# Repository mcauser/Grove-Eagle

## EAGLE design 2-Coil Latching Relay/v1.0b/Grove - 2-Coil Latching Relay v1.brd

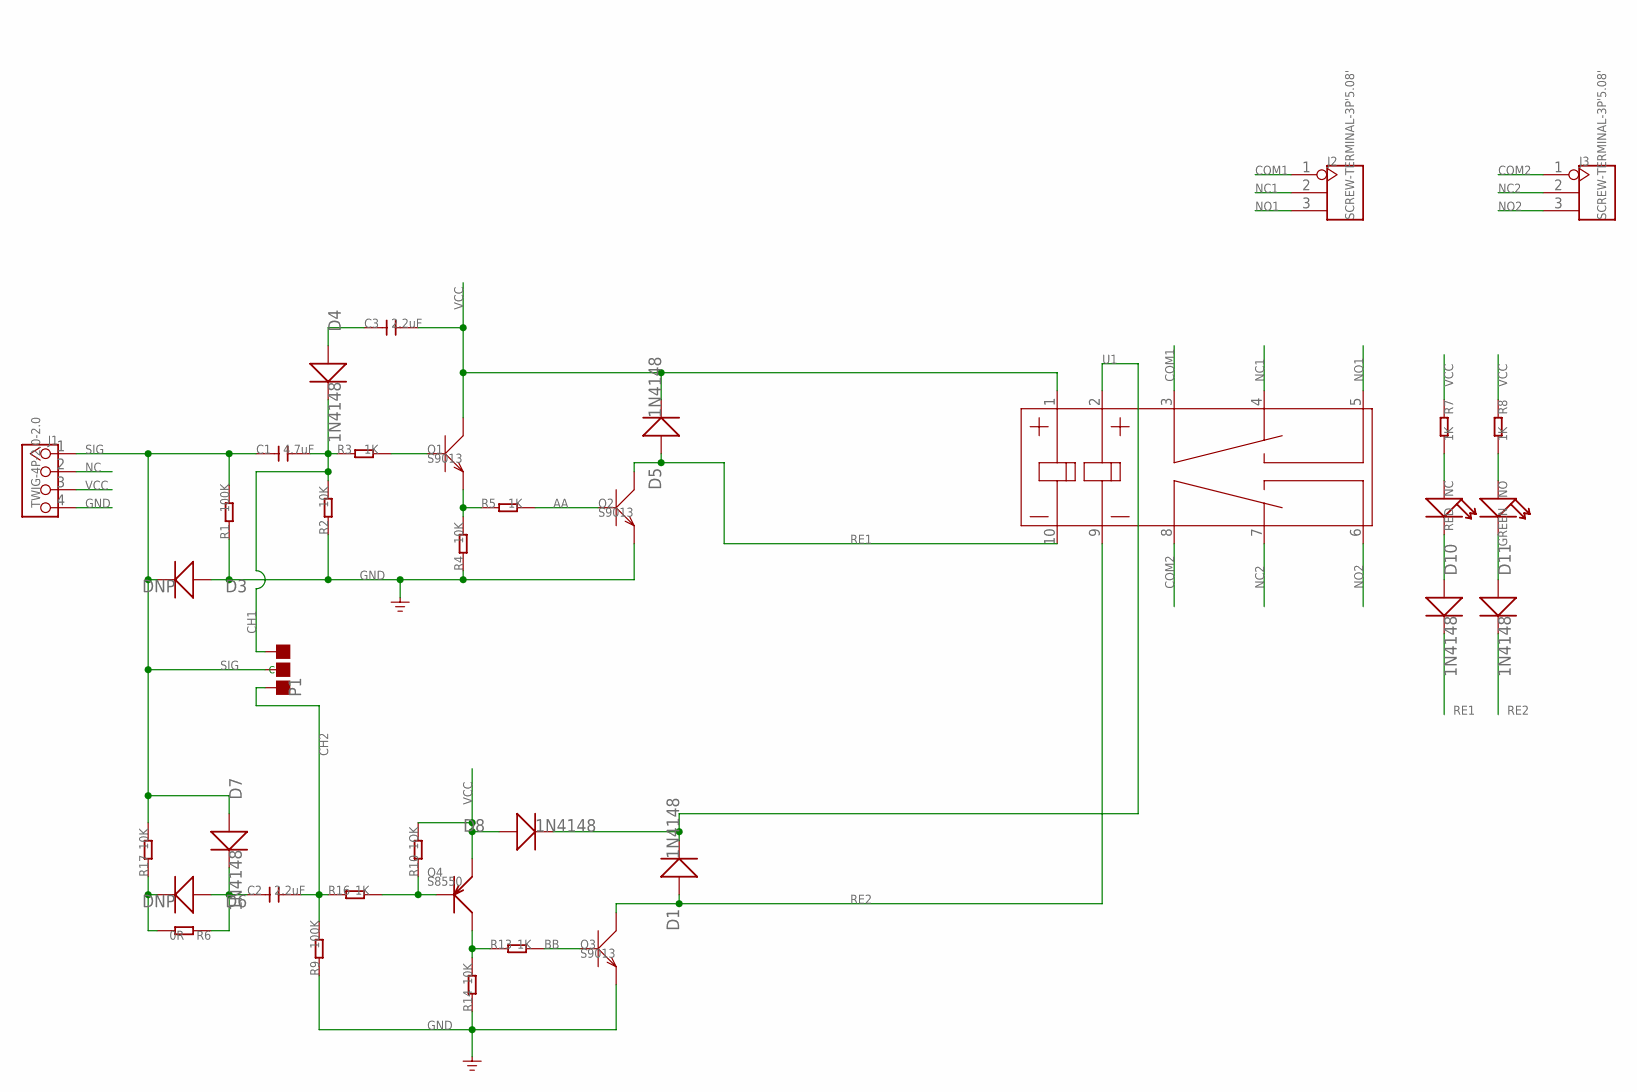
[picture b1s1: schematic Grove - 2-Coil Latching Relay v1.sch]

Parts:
C1: 4.7uF; C0805
C2, C3: 2.2uF; C0805
D1, D4, D5, D7, D8, D10, D11: 1N4148; DO-35-SMD
D3, D6: DNP; DO-35-SMD
J1: TWIG-4P-2.0-2.0; 4P-2.0
J2, J3: SCREW-TERMINAL-3P'5.08'; 3P-5.08
NC: RED; LED-0603
NO: GREEN; LED-0603
P1: PAD-JUMPER-3P-40*40; 3P-SMD-4.1X1.5
Q1, Q2, Q3: S9013; SOT23
Q4: S8550; SOT23
R1, R9: 100K; R0603
R2, R4, R14, R17: 10K; R0603
R3, R5, R7, R8, R13, R16: 1K; R0603
R6: 0R; R0603
R10: 1OK; R0603
U1: RELAY-HFD2/005-S-L2'HFD2/005-S-L2'; 10P-20.2X10.2X10.6

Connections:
AA: Q2.1 (B), R5.2
BB: Q3.1 (B), R13.2
CH1: C1.2, D4.C (-), P1.00 (L), R2.2, R3.1
CH2: C2.2, P1.11 (R), R9.2, R16.1
COM1: J2.1, U1.3 (4)
COM2: J3.1, U1.8 (13)
GND: D3.A (+), J1.4, Q2.2 (E), Q3.2 (E), R1.1, R2.1, R4.1, R9.1, R14.1
unnamed: NO.+, R8.2
unnamed: C3.1, D4.A (+)
unnamed: Q1.1 (B), R3.2
unnamed: Q1.2 (E), R4.2, R5.1
unnamed: D10.A (+), NC.-
unnamed: D11.A (+), NO.-
unnamed: NC.+, R7.2
unnamed: D6.C (-), R6.2, R17.1
unnamed: C2.1, D6.A (+), D7.C (-), R6.1
unnamed: Q4.1 (B), R10.1, R16.2
unnamed: D1.C (-), D8.C (-), U1.2
unnamed: Q4.3 (C), R13.1, R14.2
NC: J1.2
NC1: J2.2, U1.4 (6)
NC2: J3.2, U1.7 (11)
NO1: J2.3, U1.5 (8)
NO2: J3.3, U1.6 (9)
RE1: D5.A (+), D10.C (-), Q2.3 (C), U1.10 (16)
RE2: D1.A (+), D11.C (-), Q3.3 (C), U1.9 (15)
SIG: C1.1, D3.C (-), D7.A (+), J1.1, P1.MM (C), R1.2, R17.2
VCC: C3.2, D5.C (-), D8.A (+), J1.3, Q1.3 (C), Q4.2 (E), R7.1, R8.1, R10.2, U1.1

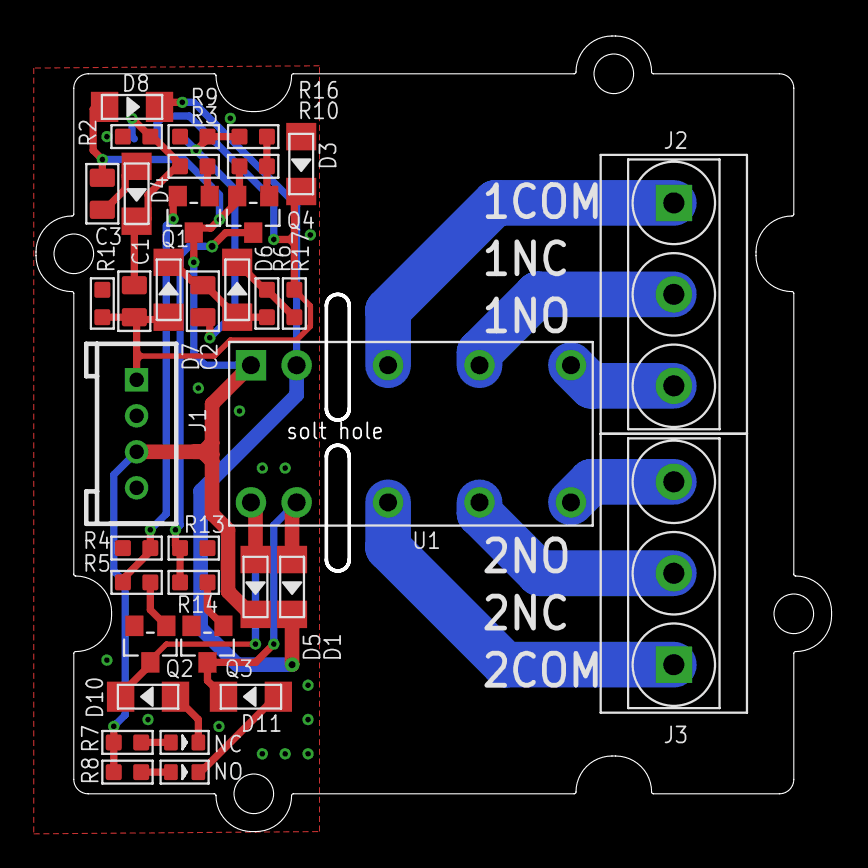
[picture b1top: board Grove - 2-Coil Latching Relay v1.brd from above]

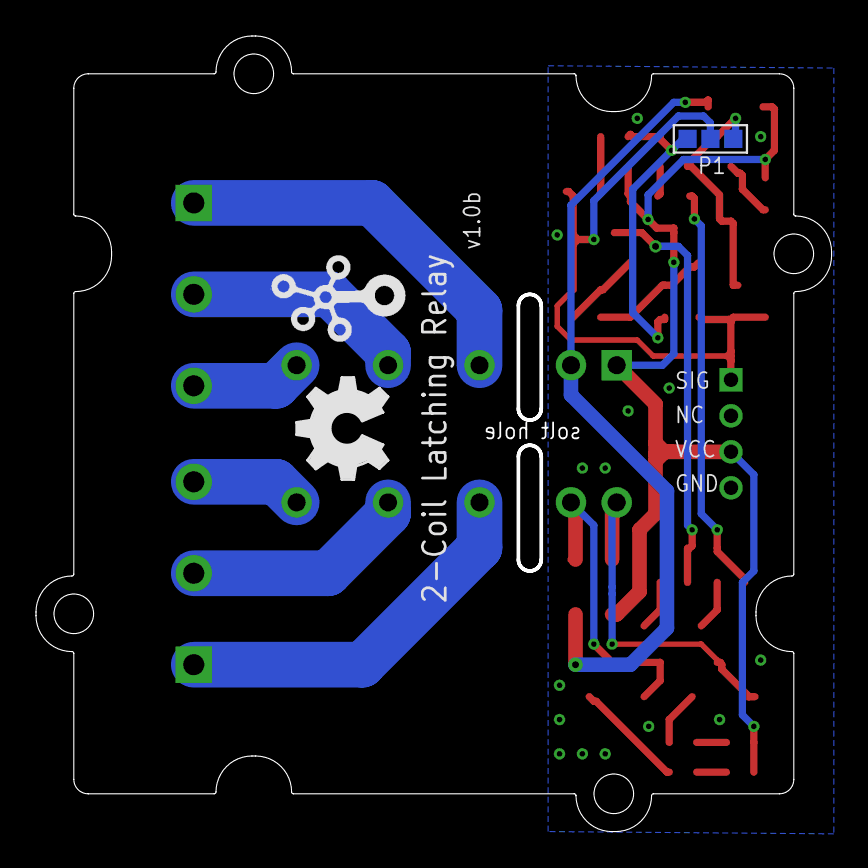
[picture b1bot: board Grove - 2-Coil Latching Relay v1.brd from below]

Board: 2 copper layers, 44.2 x 44.2 mm, 40 parts (3 on the bottom side), 27 nets.

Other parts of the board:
U$4: 2X2U-DIM-W/-DRILL
U$5: OSHW_FILLX200_NOTEXT
U$6: TWIGLOGO

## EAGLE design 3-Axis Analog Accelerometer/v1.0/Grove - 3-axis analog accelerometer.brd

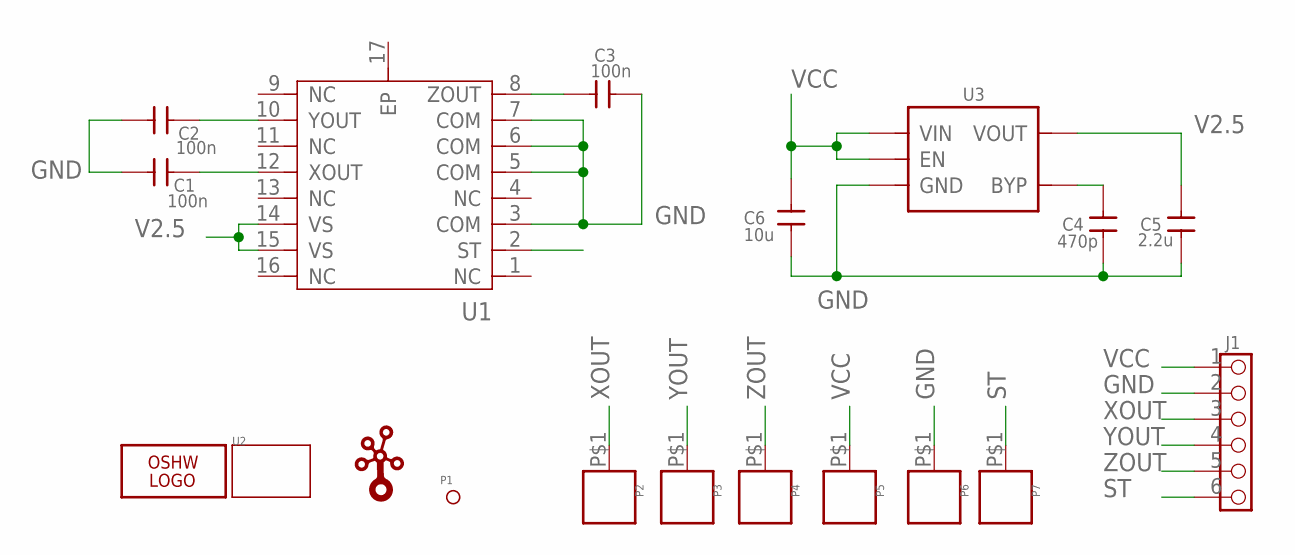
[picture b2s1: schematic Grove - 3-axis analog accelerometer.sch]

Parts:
C1, C2, C3: 100n; 0402
C4: 470p; 0603
C5: 2.2u; 0603
C6: 10u; 0603
J1: HEADER-6P-60/35MIL; 6P-2.54-60/35MIL
LOGO2: LOGO-OSHW-6MILX0200-NT; OSHW_6X200_NOTEXT
P1: PAD-MARK; ROUND-MARK-0.635
P2, P3, P4, P5, P6, P7: PAD'1X2MM'; 1P-1X2
U1: ADXL335; LFCSP16-4X4
U2: TWIG-1U; 1U-DIM-W/-DRILL
U3: MIC5205; SOT23-5
U$1: LOGO-TWIGTWIGLOGO_SMALL; TWIGLOGO_SMALL

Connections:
GND: C1.1, C2.2, C3.1, C4.1, C5.1, C6.1, J1.2, P6.P$1, U1.3 (COM), U1.5 (COM), U1.6 (COM), U1.7 (COM), U3.2 (GND)
unnamed: C4.2, U3.4 (BYP)
ST: J1.6, P7.P$1, U1.2 (ST)
V2.5: C5.2, U1.14 (VS), U1.15 (VS), U3.5 (VOUT)
VCC: C6.2, J1.1, P5.P$1, U3.1 (VIN), U3.3 (EN)
XOUT: C1.2, J1.3, P2.P$1, U1.12 (XOUT)
YOUT: C2.1, J1.4, P3.P$1, U1.10 (YOUT)
ZOUT: C3.2, J1.5, P4.P$1, U1.8 (ZOUT)

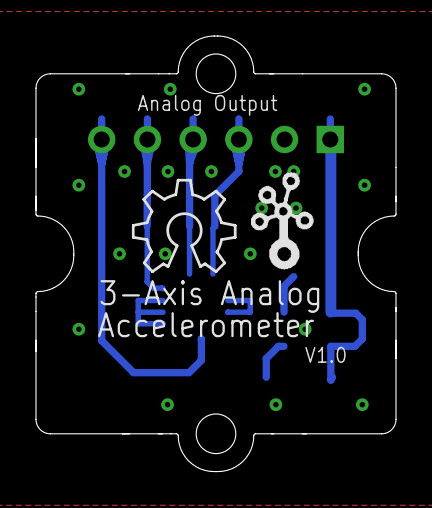
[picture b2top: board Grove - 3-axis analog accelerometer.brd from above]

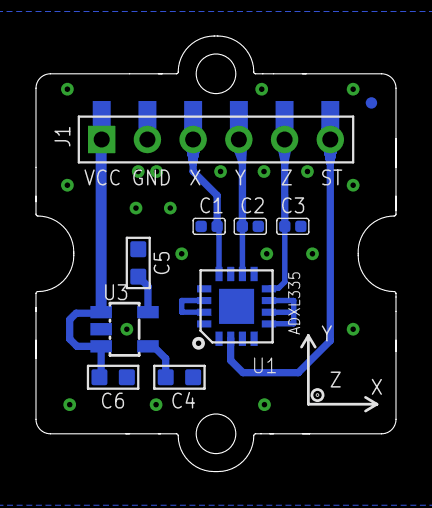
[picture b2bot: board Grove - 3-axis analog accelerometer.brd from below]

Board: 2 copper layers, 20.0 x 24.2 mm, 19 parts (17 on the bottom side), 8 nets.

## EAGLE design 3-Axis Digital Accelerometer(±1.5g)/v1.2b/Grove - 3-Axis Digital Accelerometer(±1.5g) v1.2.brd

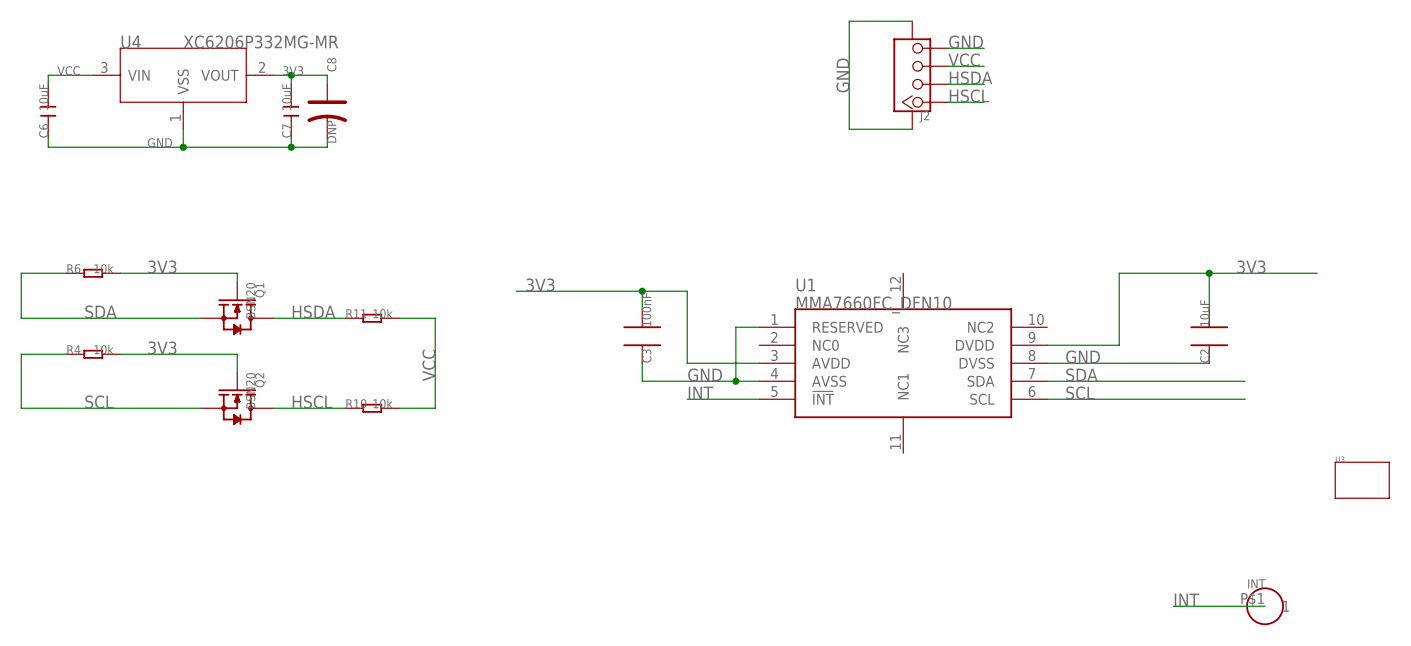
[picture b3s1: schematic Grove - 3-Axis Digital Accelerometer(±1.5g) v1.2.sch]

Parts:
C2: 10uF; 0805_S
C3: 100nF; 0603_S
C6, C7: 10uF; C0805
C8: DNP; AVX-A
INT: HEADER-1P-35; 1P-65/35MIL
J2: TWIG-4P-2.0-SMD-FEMALE-REINFORCE'DD'; 4P-SMD-2.0
Q1, Q2: BSN20; SOT23
R4, R6, R10, R11: 10k; R0603
U1: MMA7660FC_DFN10; DFN10
U3: TWIG-1U; 1U-DIM-W/-DRILL
U4: XC6206P332MG-MR; SOT23

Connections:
3V3: C2.2, C3.2, C7.2, C8.+, Q1.1 (G), Q2.1 (G), R4.2, R6.2, U1.3 (AVDD), U1.9 (DVDD), U4.2 (VOUT)
GND: C2.1, C3.1, C6.1, C7.1, C8.-, J2.4, J2.SS1, J2.SS2, U1.1 (RESERVED), U1.4 (AVSS), U1.8 (DVSS), U4.1 (VSS)
HSCL: J2.1, Q2.3 (D), R10.1
HSDA: J2.2, Q1.3 (D), R11.1
INT: INT.P$1, U1.5 (!INT)
SCL: Q2.2 (S), R4.1, U1.6 (SCL)
SDA: Q1.2 (S), R6.1, U1.7 (SDA)
VCC: C6.2, J2.3, R10.2, R11.2, U4.3 (VIN)

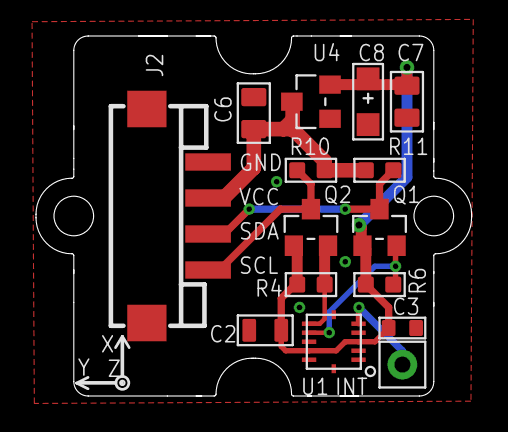
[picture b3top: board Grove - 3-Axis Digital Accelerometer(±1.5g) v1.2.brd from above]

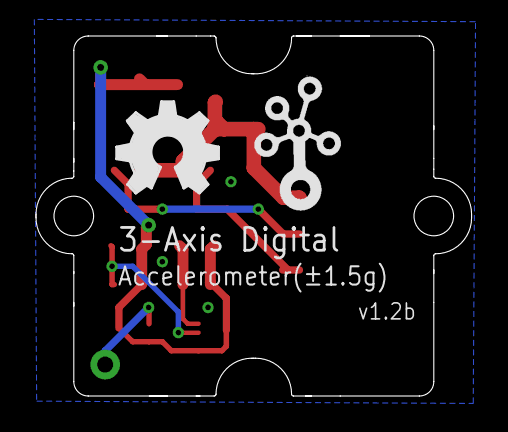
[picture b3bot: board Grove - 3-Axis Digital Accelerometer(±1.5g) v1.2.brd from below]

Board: 2 copper layers, 24.2 x 20.0 mm, 18 parts (2 on the bottom side), 8 nets.

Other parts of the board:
U$1: OSHW_FILLX200_NOTEXT
U$3: TWIGLOGO

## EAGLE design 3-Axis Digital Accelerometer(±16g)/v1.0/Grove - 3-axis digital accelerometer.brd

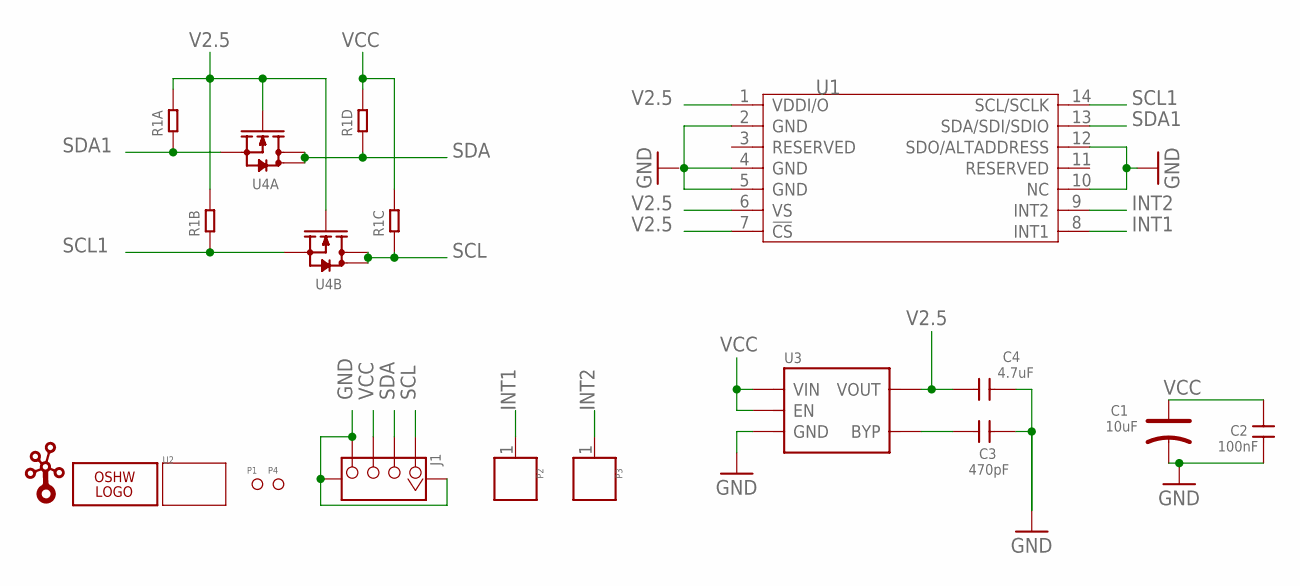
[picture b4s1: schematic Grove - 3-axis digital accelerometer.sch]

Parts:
C1: 10uF; AVX-A
C2: 100nF; 0603
C3: 470pF; 0603
C4: 4.7uF; 0603
J1: TWIG-4P-2.0-SMD-FEMALE-REINFORCE'DD'; 4P-SMD-2.0
LOGO1: LOGO-OSHW-6MILX0200-NT; OSHW_6X200_NOTEXT
P1, P4: PAD-MARK; ROUND-MARK-0.635
P2, P3: PAD'60/30'; 1P-65/35MIL
R1: R-4R-1206; 1206-8-3.3X2.4
U1: ADXL345; LGA14
U2: TWIG-1U; 1U-DIM-W/-DRILL
U3: MIC5205; SOT23-5
U4: MOSFET-DUAL-N-1206-8; 1206-8
U$1: LOGO-TWIGTWIGLOGO_SMALL; TWIGLOGO_SMALL

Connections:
GND: C1.-, C2.1, C3.1, C4.2, J1.4, J1.SS1, J1.SS2, U1.2 (GND), U1.4 (GND), U1.5 (GND), U1.10 (NC), U1.12 (SDO/ALTADDRESS), U3.2 (GND)
INT1: P2.1, U1.8 (INT1)
INT2: P3.1, U1.9 (INT2)
unnamed: C3.2, U3.4 (BYP)
SCL: J1.1, R1.3 (1), U4.5 (D), U4.6 (D)
SCL1: R1.2 (1), U1.14 (SCL/SCLK), U4.3 (S)
SDA: J1.2, R1.4 (1), U4.7 (D), U4.8 (D)
SDA1: R1.1, U1.13 (SDA/SDI/SDIO), U4.1 (S)
V2.5: C4.1, R1.7 (2), R1.8 (2), U1.1 (VDDI/O), U1.6 (VS), U1.7 (!CS), U3.5 (VOUT), U4.2 (G), U4.4 (G)
VCC: C1.+, C2.2, J1.3, R1.5 (2), R1.6 (2), U3.1 (VIN), U3.3 (EN)

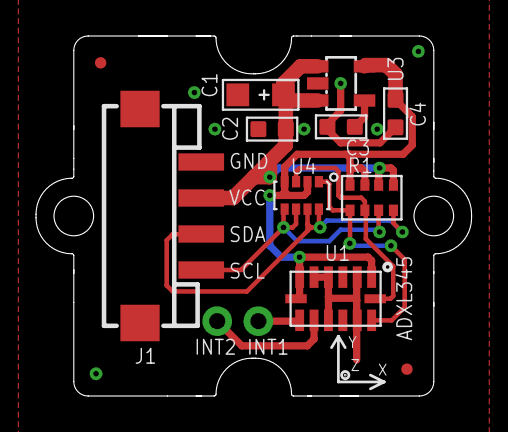
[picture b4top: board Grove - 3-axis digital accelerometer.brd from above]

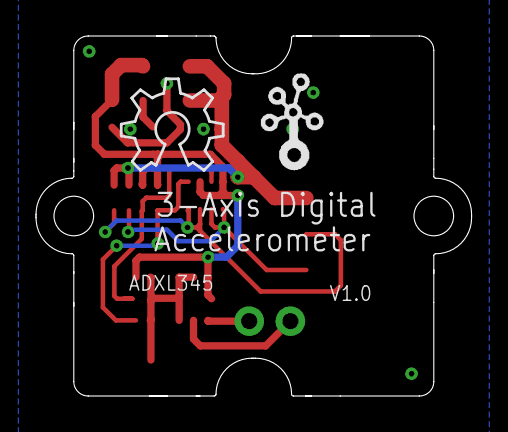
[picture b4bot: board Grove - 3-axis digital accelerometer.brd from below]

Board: 2 copper layers, 24.2 x 20.0 mm, 16 parts (2 on the bottom side), 10 nets.

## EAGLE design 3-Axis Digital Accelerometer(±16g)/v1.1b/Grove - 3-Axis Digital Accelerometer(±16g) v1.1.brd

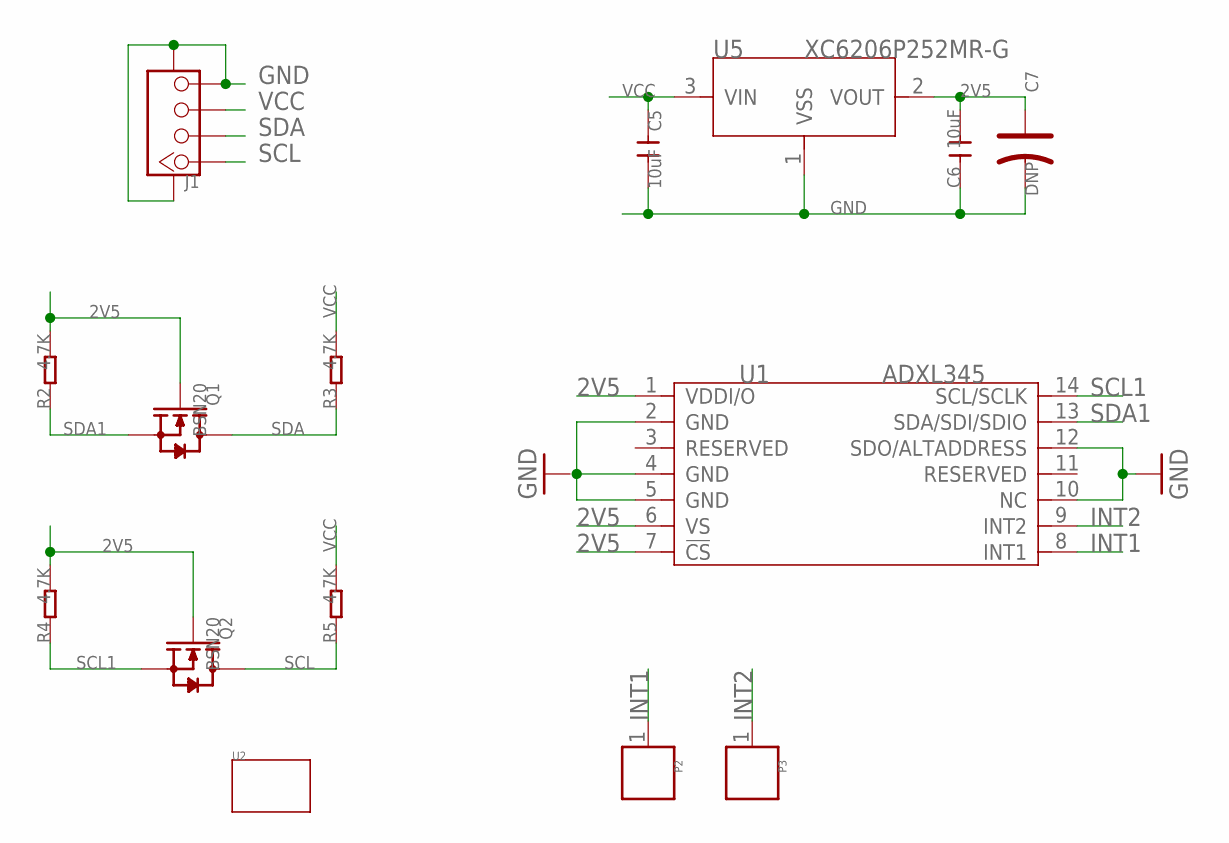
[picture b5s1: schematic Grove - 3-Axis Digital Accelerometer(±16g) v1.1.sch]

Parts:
C5, C6: 10uF; C0805
C7: DNP; AVX-A
J1: TWIG-4P-2.0-SMD-FEMALE-REINFORCE'DD'; 4P-SMD-2.0
P2, P3: PAD'60/30'; 1P-65/35MIL
Q1, Q2: BSN20; SOT23
R2, R3, R4, R5: 4.7K; R0603
U1: ADXL345; LGA14
U2: TWIG-1U; 1U-DIM-W/-DRILL
U5: XC6206P252MR-G; SOT23

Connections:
2V5: C6.2, C7.+, Q1.1 (G), Q2.1 (G), R2.2, R4.2, U1.1 (VDDI/O), U1.6 (VS), U1.7 (!CS), U5.2 (VOUT)
GND: C5.2, C6.1, C7.-, J1.4, J1.SS1, J1.SS2, U1.2 (GND), U1.4 (GND), U1.5 (GND), U1.10 (NC), U1.12 (SDO/ALTADDRESS), U5.1 (VSS)
INT1: P2.1, U1.8 (INT1)
INT2: P3.1, U1.9 (INT2)
SCL: J1.1, Q2.3 (D), R5.1
SCL1: Q2.2 (S), R4.1, U1.14 (SCL/SCLK)
SDA: J1.2, Q1.3 (D), R3.1
SDA1: Q1.2 (S), R2.1, U1.13 (SDA/SDI/SDIO)
VCC: C5.1, J1.3, R3.2, R5.2, U5.3 (VIN)

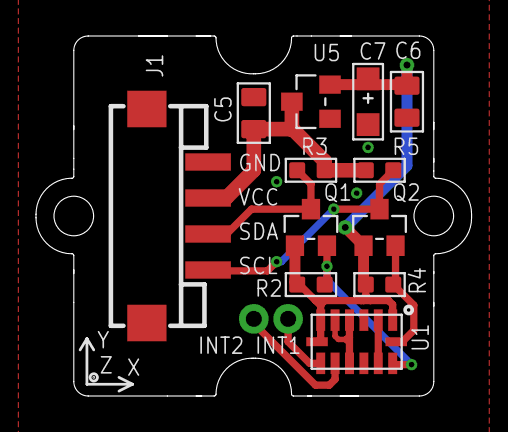
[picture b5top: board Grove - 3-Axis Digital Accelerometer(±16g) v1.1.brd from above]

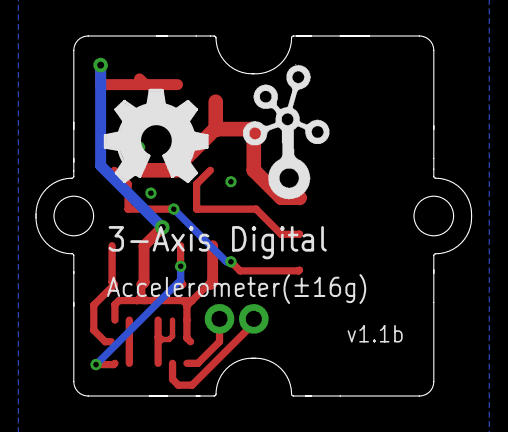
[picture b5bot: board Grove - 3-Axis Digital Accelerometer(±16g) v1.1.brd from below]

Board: 2 copper layers, 24.2 x 20.0 mm, 17 parts (2 on the bottom side), 9 nets.

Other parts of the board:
U$1: OSHW_FILLX200_NOTEXT
U$3: TWIGLOGO
